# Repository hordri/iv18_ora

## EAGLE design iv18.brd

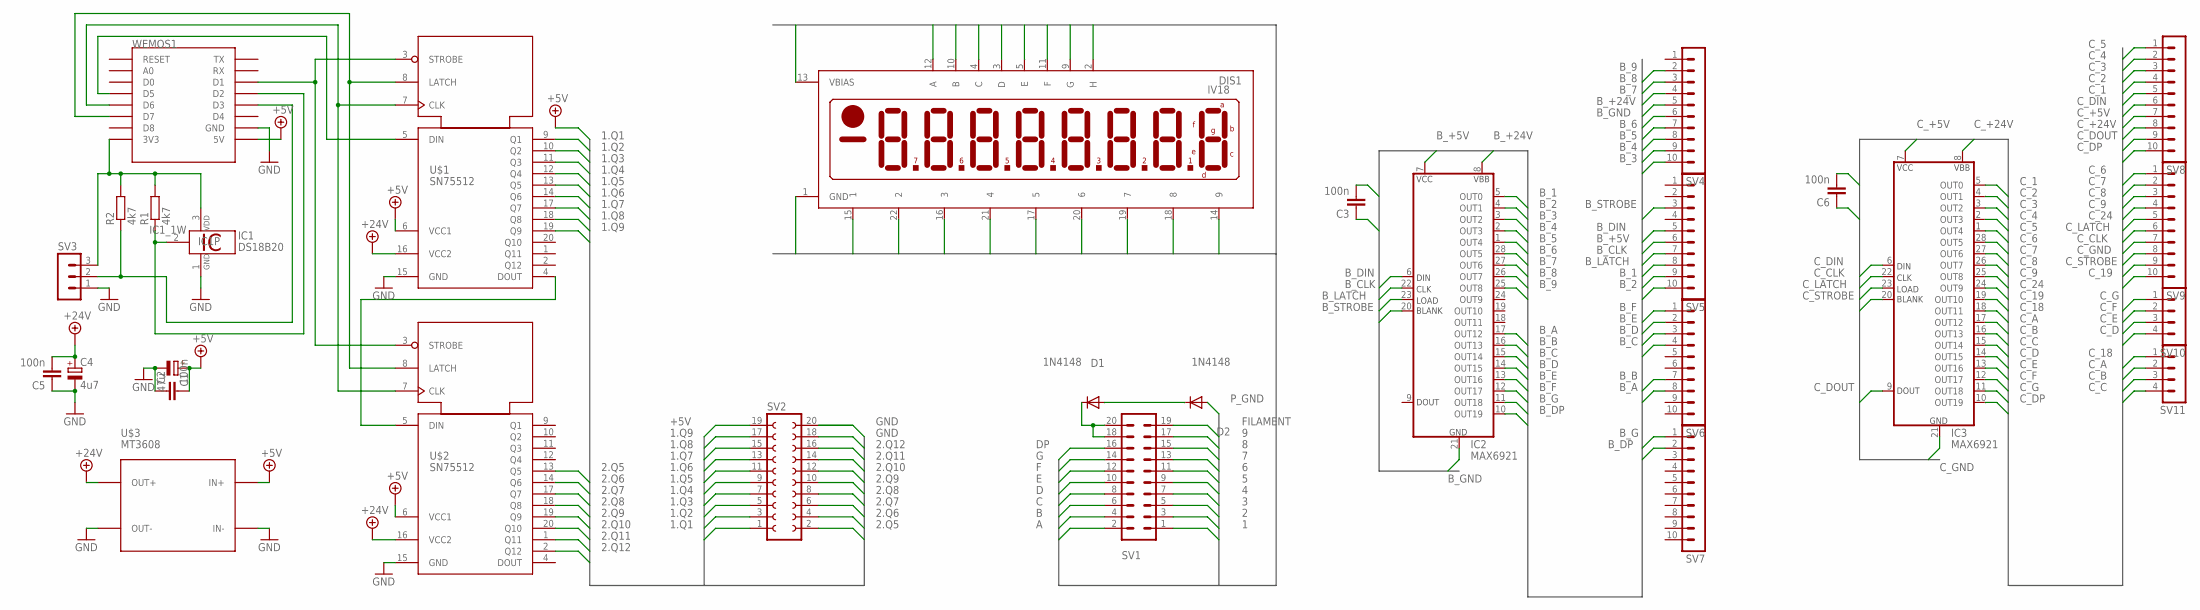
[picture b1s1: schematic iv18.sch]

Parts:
C1: 47u; E2,5-7
C2, C3, C5, C6: 100n; C025-030X050
C4: 4u7; E2,5-5
D1, D2: 1N4148; DO35-7
DIS1: IV18
IC1: DS18B20; TO92-
IC2, IC3: MAX6921; TSSOP-28
R1, R2: 4k7; M1206
SV1: MA10-2W
SV2: FE10-2
SV3: MA03-1
SV4, SV5, SV6, SV7, SV8, SV9: MA10-1
SV10, SV11: MA04-1
U$1, U$2: SN75512; DIL20
U$3: MT3608; DC-DC-STEP-UP-MT3608
WEMOS1: WEMOS-D1-MINI

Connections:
1: DIS1.15 (1), SV1.1
1.Q1: SV2.1, U$1.9 (Q1)
1.Q2: SV2.3, U$1.10 (Q2)
1.Q3: SV2.5, U$1.11 (Q3)
1.Q4: SV2.7, U$1.12 (Q4)
1.Q5: SV2.9, U$1.13 (Q5)
1.Q6: SV2.11, U$1.14 (Q6)
1.Q7: SV2.13, U$1.17 (Q7)
1.Q8: SV2.15, U$1.18 (Q8)
1.Q9: SV2.17, U$1.19 (Q9)
2: DIS1.22 (2), SV1.3
2.Q5: SV2.2, U$2.13 (Q5)
2.Q6: SV2.4, U$2.14 (Q6)
2.Q7: SV2.6, U$2.17 (Q7)
2.Q8: SV2.8, U$2.18 (Q8)
2.Q9: SV2.10, U$2.19 (Q9)
2.Q10: SV2.12, U$2.20 (Q10)
2.Q11: SV2.14, U$2.1 (Q11)
2.Q12: SV2.16, U$2.2 (Q12)
3: DIS1.16 (3), SV1.5
4: DIS1.21 (4), SV1.7
5: DIS1.17 (5), SV1.9
6: DIS1.20 (6), SV1.11
7: DIS1.19 (7), SV1.13
8: DIS1.18 (8), SV1.15
9: DIS1.14 (9), SV1.17
+5V: C1.+, C2.2, SV2.19, U$1.6 (VCC1), U$2.6 (VCC1), U$3.IN+, WEMOS1.5V
+24V: C4.+, C5.2, U$1.16 (VCC2), U$2.16 (VCC2), U$3.OUT+
A: DIS1.12 (A), SV1.2
B: DIS1.10 (B), SV1.4
B_1: IC2.5 (OUT0), SV5.9
B_2: IC2.4 (OUT1), SV5.10
B_3: IC2.3 (OUT2), SV4.10
B_4: IC2.2 (OUT3), SV4.9
B_5: IC2.1 (OUT4), SV4.8
B_6: IC2.28 (OUT5), SV4.7
B_7: IC2.27 (OUT6), SV4.4
B_8: IC2.26 (OUT7), SV4.3
B_9: IC2.25 (OUT8), SV4.2
B_+5V: C3.2, IC2.7 (VCC), SV5.6
B_+24V: IC2.8 (VBB), SV4.5
B_A: IC2.17 (OUT12), SV6.8
B_B: IC2.16 (OUT13), SV6.7
B_C: IC2.15 (OUT14), SV6.4
B_CLK: IC2.22 (CLK), SV5.7
B_D: IC2.14 (OUT15), SV6.3
B_DIN: IC2.6 (DIN), SV5.5
B_DP: IC2.10 (OUT19), SV7.2
B_E: IC2.13 (OUT16), SV6.2
B_F: IC2.12 (OUT17), SV6.1
B_G: IC2.11 (OUT18), SV7.1
B_GND: C3.1, IC2.21 (GND), SV4.6
B_LATCH: IC2.23 (LOAD), SV5.8
B_STROBE: IC2.20 (BLANK), SV5.3
C: DIS1.4 (C), SV1.6
C_1: IC3.5 (OUT0), SV8.5
C_2: IC3.4 (OUT1), SV8.4
C_3: IC3.3 (OUT2), SV8.3
C_4: IC3.2 (OUT3), SV8.2
C_5: IC3.1 (OUT4), SV8.1
C_6: IC3.28 (OUT5), SV9.1
C_7: IC3.27 (OUT6), SV9.2
C_8: IC3.26 (OUT7), SV9.3
C_9: IC3.25 (OUT8), SV9.4
C_18: IC3.18 (OUT11), SV11.1
C_19: IC3.19 (OUT10), SV9.10
C_24: IC3.24 (OUT9), SV9.5
C_+5V: C6.2, IC3.7 (VCC), SV8.7
C_+24V: IC3.8 (VBB), SV8.8
C_A: IC3.17 (OUT12), SV11.2
C_B: IC3.16 (OUT13), SV11.3
C_C: IC3.15 (OUT14), SV11.4
C_CLK: IC3.22 (CLK), SV9.7
C_D: IC3.14 (OUT15), SV10.4
C_DIN: IC3.6 (DIN), SV8.6
C_DOUT: IC3.9 (DOUT), SV8.9
C_DP: IC3.10 (OUT19), SV8.10
C_E: IC3.13 (OUT16), SV10.3
C_F: IC3.12 (OUT17), SV10.2
C_G: IC3.11 (OUT18), SV10.1
C_GND: C6.1, IC3.21 (GND), SV9.8
C_LATCH: IC3.23 (LOAD), SV9.6
C_STROBE: IC3.20 (BLANK), SV9.9
D: DIS1.3 (D), SV1.8
DP: DIS1.2 (H), SV1.16
E: DIS1.5 (E), SV1.10
F: DIS1.11 (F), SV1.12
FILAMENT: DIS1.13 (VBIAS), SV1.19
G: DIS1.9 (G), SV1.14
GND: C1.-, C2.1, C4.-, C5.1, IC1.1 (GND), SV2.18, SV2.20, SV3.1, U$1.15 (GND), U$2.15 (GND), U$3.IN-, U$3.OUT-, WEMOS1.GND
unnamed: U$1.5 (DIN), WEMOS1.D5
unnamed: U$1.7 (CLK), U$2.7 (CLK), WEMOS1.D6
unnamed: U$1.8 (LATCH), U$2.8 (LATCH), WEMOS1.D7
unnamed: U$1.3 (STROBE), U$2.3 (STROBE), WEMOS1.D1
unnamed: U$1.4 (DOUT), U$2.5 (DIN)
unnamed: D1.A, D2.C
unnamed: IC1.3 (VDD), R1.2, R2.2, SV3.3, WEMOS1.3V3
unnamed: IC1.2 (1W), R1.1, WEMOS1.D2
unnamed: R2.1, SV3.2, WEMOS1.D3
unnamed: D1.C, SV1.18, SV1.20
P_GND: D2.A, DIS1.1 (GND)

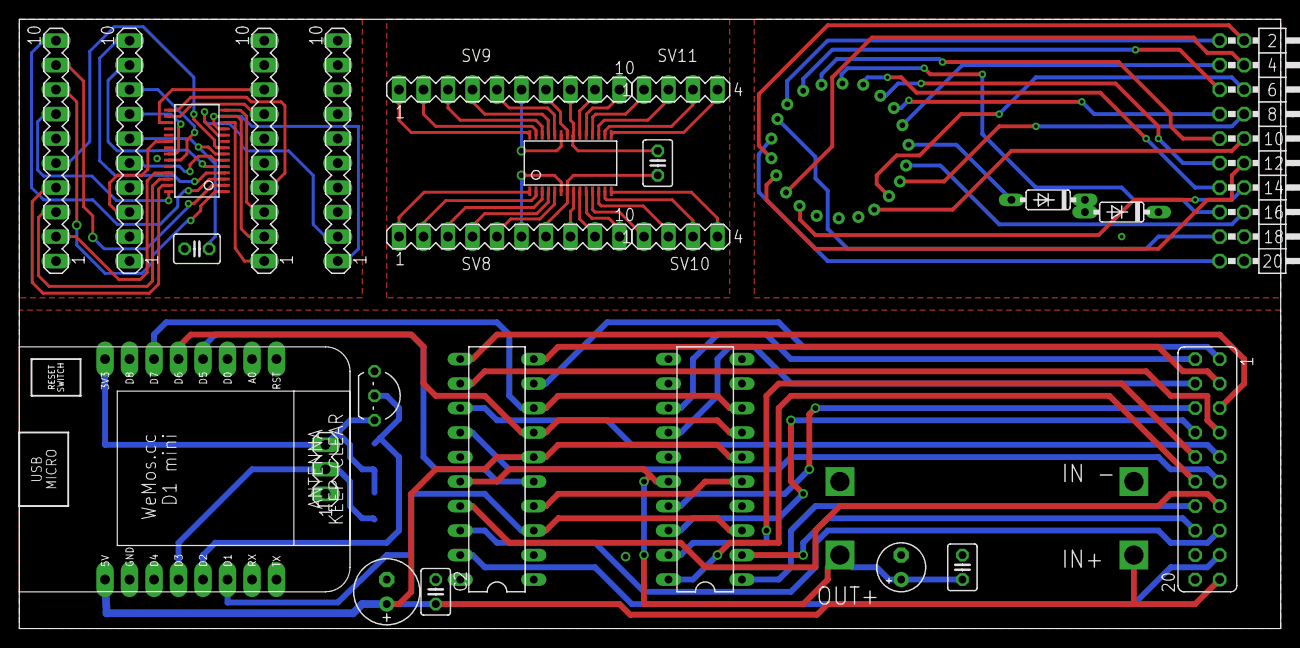
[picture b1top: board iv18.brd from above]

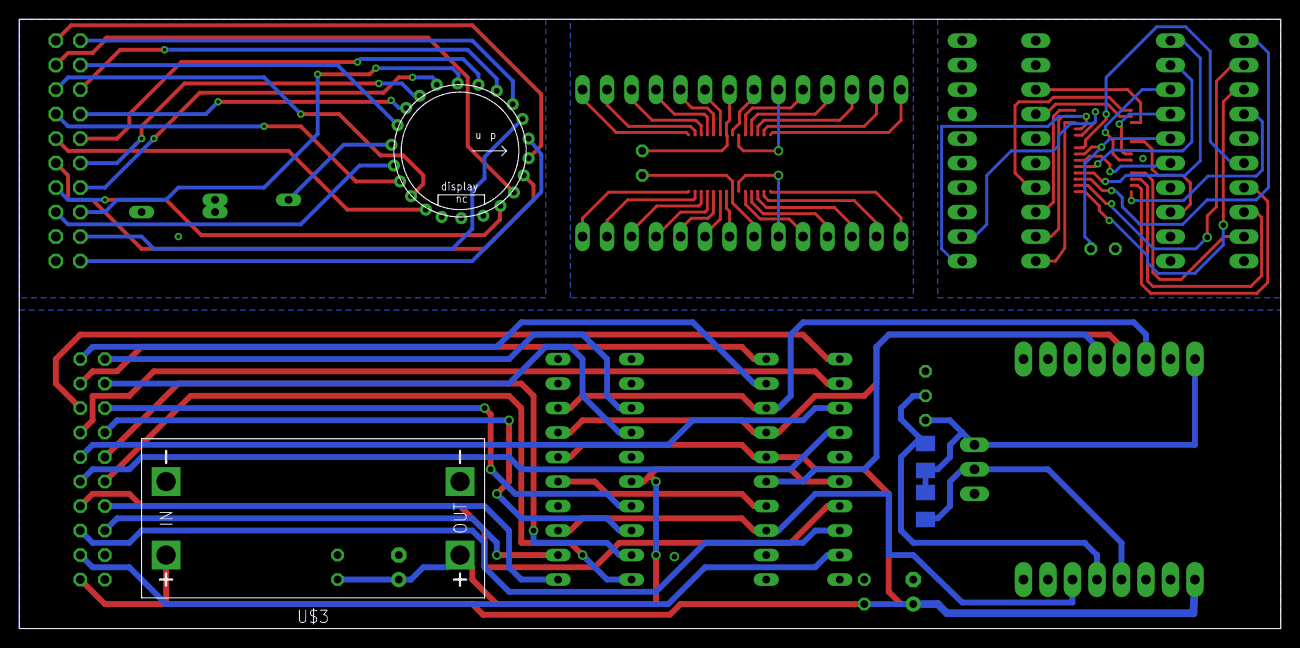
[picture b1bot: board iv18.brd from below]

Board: 2 copper layers, 130.8 x 63.2 mm, 29 parts (4 on the bottom side), 101 nets.

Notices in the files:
parts and their libraries:
diy-modules: Released under the Creative Commons Attribution 4.0 International License: http://creativecommons.org/licenses/by/4.0
